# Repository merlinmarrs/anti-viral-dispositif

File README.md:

# anti-viral-dispositif

Developed by Fablab Digiscope, France

A main board and secondary board to control a disinfection chamber based on this tutorial: http://www.needlab.org/face-masks-disinfection-device

The PDF shows step by step instructions of the assembly.

Here is the BOM:

Standard components:

7 segment display x2
595 Shift Register x2 
LED x 2
Photocell
Piezo
Atmega 328p
micro-swith (*CHECK MAX VOLT + AMP RATING*)

exotic components:

lampe UV-C à Amazon.fr:

https://www.amazon.fr/Germicide-Ultraviolet-st%C3%A9rilisateur-Submersible-radiations/dp/B07Y82SM36/ref=sr_1_4?__mk_fr_FR=%C3%85M%C3%85%C5%BD%C3%95%C3%91&dchild=1&keywords=uv+aquarium+sterilizer&qid=1587383305&s=hi&sr=1-4-catcorr

2. MLX90614 (pas en rayon a Mouser, Farnell, Sparkfun, Polulu ou
Adafruit) à  Digikey (ou c'est "hors prix") ou Amazon.fr:

https://www.digikey.com/product-detail/en/melexis-technologies-nv/MLX90614ESF-DCA-000-TU/MLX90614ESF-DCA-000-TU-ND/2025323

https://www.amazon.fr/MLX90614ESF-MLX90614ESF-BAA-000-TU-ND-thermom%C3%A8tre-infrarouge-compatible/dp/B07JBKM2K3/ref=sr_1_1?__mk_fr_FR=%C3%85M%C3%85%C5%BD%C3%95%C3%91&dchild=1&keywords=MLX90614&qid=1587470750&s=hi&sr=1-1-catcorr

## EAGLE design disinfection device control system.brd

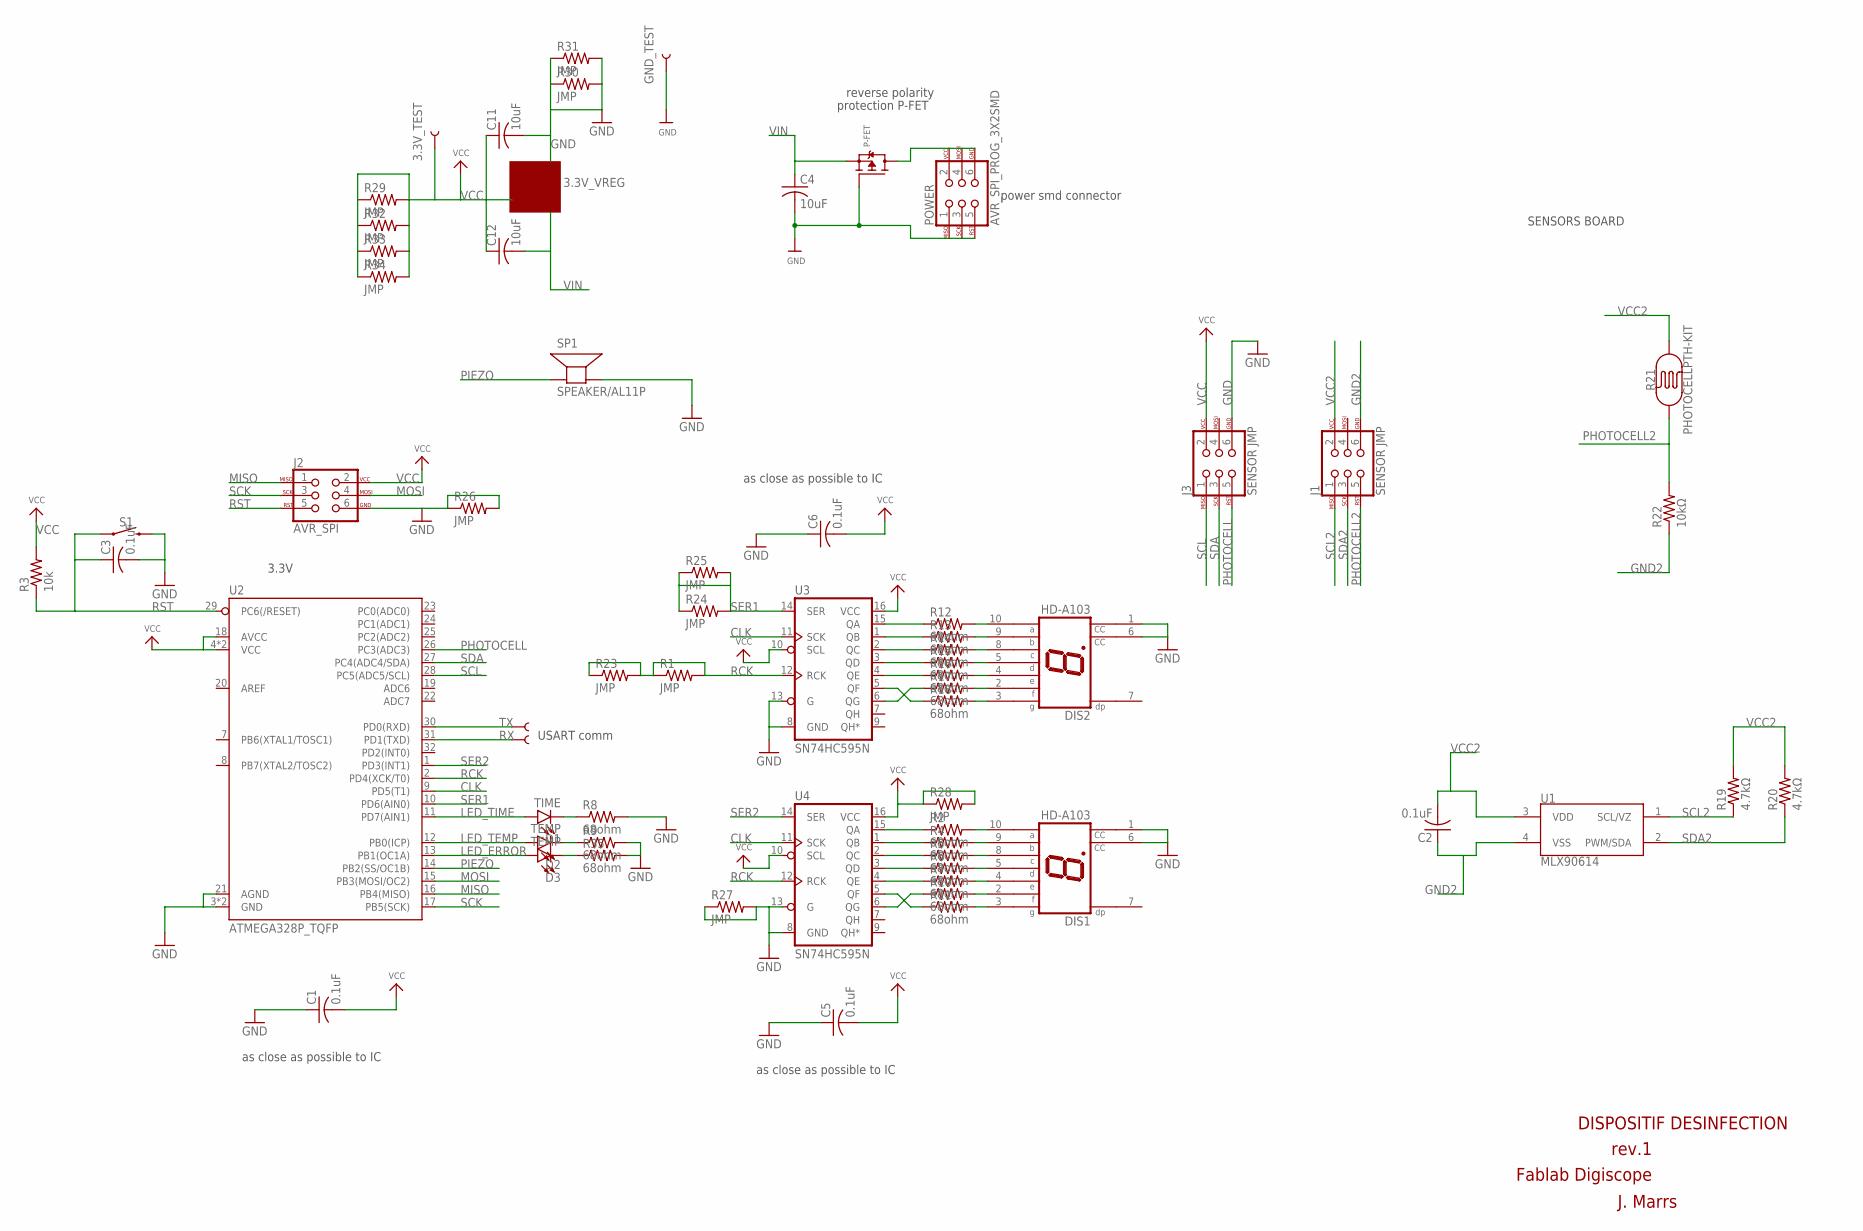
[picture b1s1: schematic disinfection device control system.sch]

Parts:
3.3V_TEST: TEST-POINT3; PAD.03X.03
3.3V_VREG: MOSFET_PCH-DMG2305UX-7; SOT23-3
C1, C2, C3, C5, C6: 0.1uF; C1206
C4, C11, C12: 10uF; C1206
D1: TIME; LED-1206
D2, D3: TEMP; LED-1206
DIS1, DIS2: HD-A103; HDSP-A
GND_TEST: TEST-POINT3; PAD.03X.03
J1, J3: SENSOR JMP; 2X3_SMT_POSTS
J2: AVR_SPI; 2X3_SMT_POSTS
P-FET: MOSFET-PWIDE; SOT23-WIDE
POWER: AVR_SPI_PROG_3X2SMD; 2X3_SMT_POSTS
R1, R23, R24, R25, R26, R27, R28, R29, R30, R31, R32, R33, R34: JMP; R1206
R2, R4, R5, R6, R7, R8, R9, R10, R11, R12, R13, R14, R15, R16, R17, R18, R35: 68ohm; R1206
R3: 10k; R1206
R19, R20: 4.7kΩ; R1206
R21: PHOTOCELLPTH-KIT; PHOTOCELL-KIT
R22: 10kΩ; R1206
RX: TEST-POINT3; PAD.03X.03
S1: MOMENTARY-SWITCH-SPST-PTH-6.0MM; TACTILE_SWITCH_PTH_6.0MM
SP1: SPEAKER/AL11P; AL11P
TX: TEST-POINT3; PAD.03X.03
U1: MLX90614; TO-39
U2: ATMEGA328P_TQFP; TQFP32-08
U3, U4: SN74HC595N; DIP16

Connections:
CLK: U2.9 (PD5(T1)), U3.11 (SCK), U4.11 (SCK)
GND: 3.3V_VREG.3 (D), C1.1, C3.2, C4.2, C5.1, C6.1, C11.2, DIS1.1 (CC), DIS1.6 (CC), DIS2.1 (CC), DIS2.6 (CC), GND_TEST.P$1, J2.6, J3.6, P-FET.1 (G), POWER.1, POWER.3, POWER.5, R8.2, R9.2, R26.1, R26.2, R27.1, R27.2, R30.1, R30.2, R31.1, R31.2, R35.2, S1.3 (2), SP1.-, U2.3 (GND), U2.5 (GND), U2.21 (AGND), U3.8 (GND), U3.13 (G), U4.8 (GND), U4.13 (G)
GND2: C2.1, J1.6, R22.1, U1.4 (VSS)
LED_ERROR: D3.A, U2.13 (PB1(OC1A))
LED_TEMP: D2.A, U2.12 (PB0(ICP))
LED_TIME: D1.A, U2.11 (PD7(AIN1))
MISO: J2.1, U2.16 (PB4(MISO))
MOSI: J2.4, U2.15 (PB3(MOSI/OC2))
unnamed: DIS1.10 (A), R2.2
unnamed: DIS1.9 (B), R4.2
unnamed: DIS1.8 (C), R5.2
unnamed: DIS1.5 (D), R6.2
unnamed: TX.P$1, U2.30 (PD0(RXD))
unnamed: RX.P$1, U2.31 (PD1(TXD))
unnamed: DIS1.4 (E), R7.2
unnamed: R2.1, U4.15 (QA)
unnamed: R4.1, U4.1 (QB)
unnamed: D2.C, R9.1
unnamed: DIS1.2 (F), R10.2
unnamed: DIS1.3 (G), R11.2
unnamed: R5.1, U4.2 (QC)
unnamed: R6.1, U4.3 (QD)
unnamed: R7.1, U4.4 (QE)
unnamed: R10.1, U4.6 (QG)
unnamed: R11.1, U4.5 (QF)
unnamed: R17.1, U3.6 (QG)
unnamed: R18.1, U3.5 (QF)
unnamed: DIS2.10 (A), R12.2
unnamed: DIS2.9 (B), R13.2
unnamed: DIS2.8 (C), R14.2
unnamed: DIS2.5 (D), R15.2
unnamed: DIS2.4 (E), R16.2
unnamed: DIS2.2 (F), R17.2
unnamed: DIS2.3 (G), R18.2
unnamed: R12.1, U3.15 (QA)
unnamed: R13.1, U3.1 (QB)
unnamed: R14.1, U3.2 (QC)
unnamed: R15.1, U3.3 (QD)
unnamed: R16.1, U3.4 (QE)
unnamed: D3.C, R35.1
PHOTOCELL: J3.5, U2.26 (PC3(ADC3))
PHOTOCELL2: J1.5, R21.1, R22.2
PIEZO: SP1.+, U2.14 (PB2(SS/OC1B))
PWRIN: P-FET.3 (D), POWER.2, POWER.4, POWER.6
RCK: R1.1, R1.2, R23.1, R23.2, U2.2 (PD4(XCK/T0)), U3.12 (RCK), U4.12 (RCK)
RST: C3.1, J2.5, R3.1, S1.1, U2.29 (PC6(/RESET))
SCK: J2.3, U2.17 (PB5(SCK))
SCL: J3.1, U2.28 (PC5(ADC5/SCL))
SCL2: J1.1, R19.1, U1.1 (SCL/VZ)
SDA: J3.3, U2.27 (PC4(ADC4/SDA))
SDA2: J1.3, R20.1, U1.2 (PWM/SDA)
SER1: R24.1, R24.2, R25.1, R25.2, U2.10 (PD6(AIN0)), U3.14 (SER)
SER2: U2.1 (PD3(INT1)), U4.14 (SER)
TIME: D1.C, R8.1
VCC: 3.3V_TEST.P$1, 3.3V_VREG.1 (G), C1.2, C5.2, C6.2, C11.1, C12.1, J2.2, J3.2, R3.2, R28.1, R28.2, R29.1, R29.2, R32.1, R32.2, R33.1, R33.2, R34.1, R34.2, U2.4 (VCC), U2.6 (VCC), U2.18 (AVCC), U3.10 (SCL), U3.16 (VCC), U4.10 (SCL), U4.16 (VCC)
VCC2: C2.2, J1.2, R19.2, R20.2, R21.2, U1.3 (VDD)
VIN: 3.3V_VREG.2 (S), C4.1, C12.2, P-FET.2 (S)

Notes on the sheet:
power smd connector
DISPOSITIF DESINFECTION
rev.1
Fablab Digiscope
J. Marrs
USART comm
as close as possible to IC
reverse polarity
protection P-FET
3.3V
SENSORS BOARD

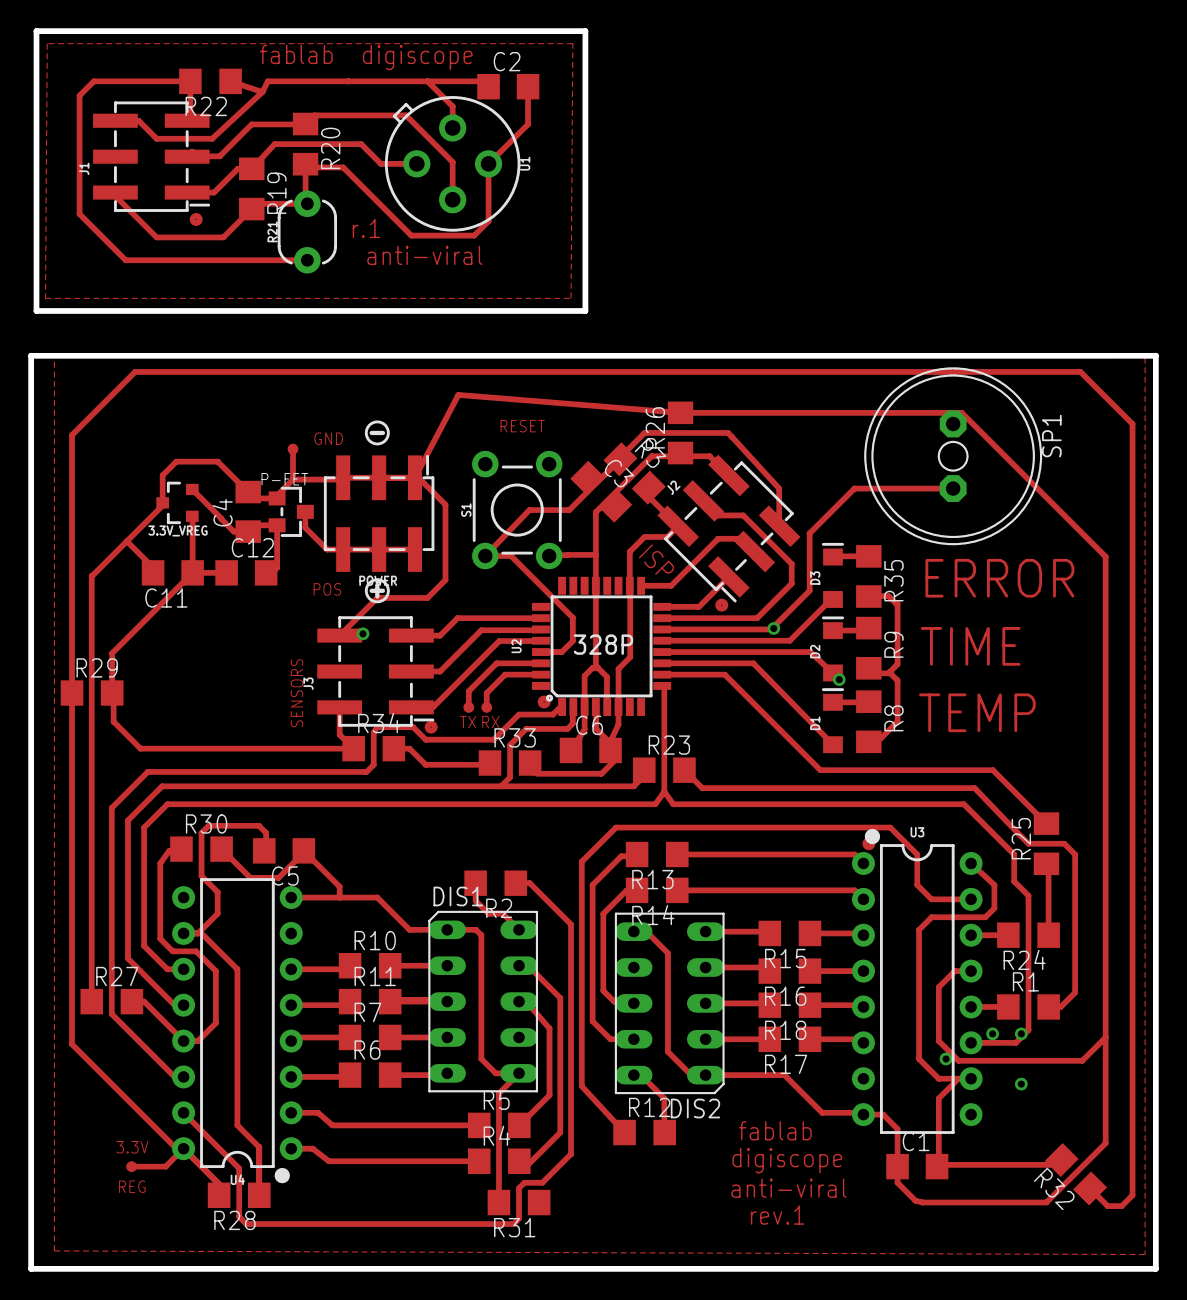
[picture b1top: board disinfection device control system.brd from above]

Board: 2 copper layers, 79.6 x 87.6 mm, 66 parts (0 on the bottom side), 57 nets.

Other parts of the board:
U$15: SYMBOL_PLUS
U$16: SYMBOL_MINUS

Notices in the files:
parts and their libraries:
SparkFun-IC-Microcontroller: Licensing: Creative Commons ShareAlike 4.0 International - https://creativecommons.org/licenses/by-sa/4.0
